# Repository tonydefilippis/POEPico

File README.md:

# POE Pico
"POE Pico" is a PCBA design for a RP2040 "Pi Pico" configured to support 40W active POE with Ethernet <-> USB conversion. 
# Diagram
Pre-print, the following 3D Views are available, but are not fully representative of the final product:
<br />Top<br />

<br />Bottom<br />

A PDF export of the schematic sheets for reference can be found [here](documentation/POEPico.pdf).
# Feature List
## Components
The USB to Ethernet conversion IC is a [LAN9500A](https://www.microchip.com/en-us/product/lan9500a). The board features a 40W active POE power/data supply input with a fully-isolated 12 VDC @ 2A Flyback courtesy of an [LT4295](https://www.analog.com/media/en/technical-documentation/data-sheets/LT4295.pdf). Downstream of the flyback is a 12V to 5V buck converter and 3.3V power rails. Ethernet magnetics and LEDs are fully integrated by the RJ45 connector. 

Alternatively, the board supports bringup of the RP2040 and power through the Micro-B connector. Powering the PCBA through the 5V Micro-B connector will also power the 3.3V rail. 
## Pins
Header pins expose standard RP2040 GPIO, including an isolated 12V, 5V, and 3.3V power rail.
| Purpose | Pin | Pin | Purpose | 
| -------- | ------- | ------- | ------- |
| GND | J21.1 | J21.2 | +3V3 |
| GND | J21.3 | J21.4 | GPIO0 |
| GND | J21.5 | J21.6 | GPIO1 |
| GND | J21.7 | J21.8 | GPIO2 |
| GND | J21.9 | J21.10 | GPIO3 |
| GND | J21.11 | J21.12 | GPIO4 |
| GND | J21.13 | J21.14 | GPIO5 |
| GND | J21.15 | J21.16 | GPIO6 |
| GND | J21.17 | J21.18 | GPIO7 |
| GND | J21.19 | J21.20 | GPIO8 |
| GND | J21.21 | J21.22 | GPIO9 |
| GND | J21.23 | J21.24 | GPIO10 |
| GND | J21.25 | J21.26 | GPIO11 |
| GND | J21.27 | J21.28 | GPIO12 |
| GND | J21.29 | J21.30 | GPIO13 |
| GND | J21.31 | J21.32 | GPIO14 |
| GND | J21.33 | J21.34 | GPIO15 |
| GND | J21.35 | J21.36 | +5V0 |

| Purpose | Pin | Pin | Purpose |
| -------- | ------- | ------- | ------- |
| SWCLK | J22.1 | J22.2 | GND |
| SWD | J22.3 | J22.4 | GND |
| RUN | J22.5 | J22.6 | GND |
| GPIO16 | J22.7 | J22.8 | GND |
| GPIO17 | J22.9 | J22.10 | GND |
| GPIO18 | J22.11 | J22.12 | GND |
| GPIO19 | J22.13 | J22.14 | GND |
| GPIO20 | J22.15 | J22.16 | GND |
| GPIO21 | J22.17 | J22.18 | GND |
| GPIO22 | J22.19 | J22.20 | GND |
| GPIO23 | J22.21 | J22.22 | GND |
| GPIO24 | J22.23 | J22.24 | GND |
| GPIO25 | J22.25 | J22.26 | GND |
| GPIO26 | J22.27 | J22.28 | GND |
| GPIO27 | J22.29 | J22.30 | GND |
| GPIO28 | J22.31 | J22.32 | GND |
| GPIO29 | J22.33 | J22.34 | GND |
| +12V0 | J22.35 | J22.26 | GND |

# Assembly
To be assembled as a 4-layer PCB, with associated BOM. Components to be placed on top and bottom of board. BOM has been edited to support JLCPCB quoting. Approximate cost estimate as of 21/10/2024 is $60/pc, including fabrication, components, assembly, and shipping.

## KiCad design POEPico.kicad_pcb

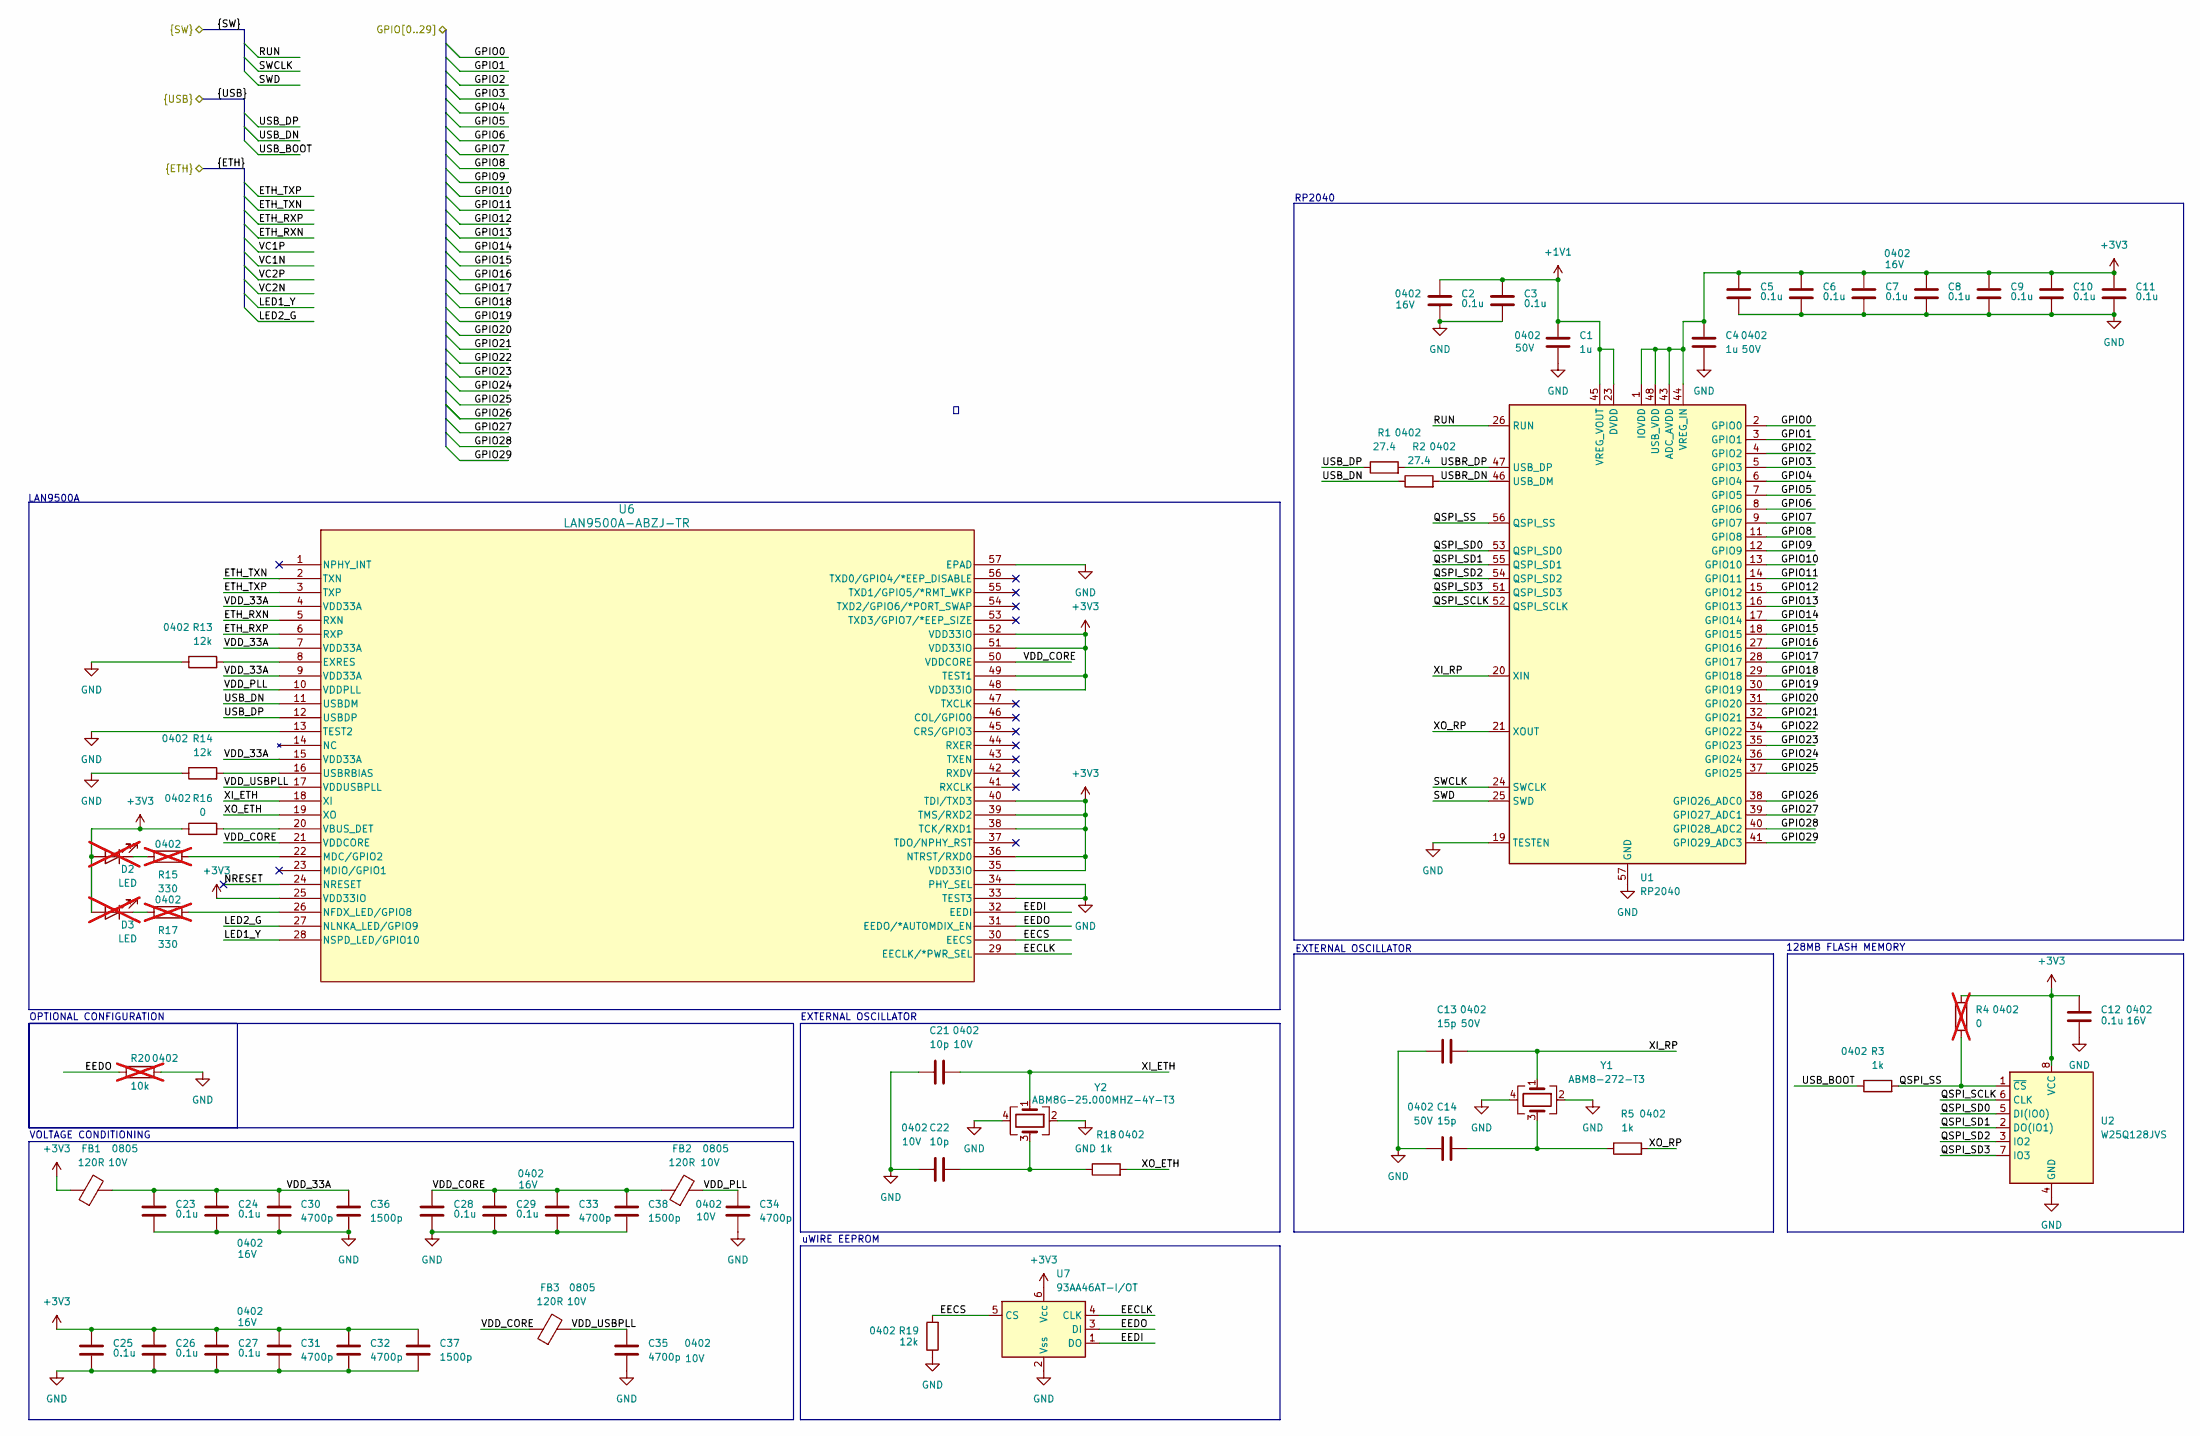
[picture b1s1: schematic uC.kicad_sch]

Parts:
C1, C4: 1u; C_0402_1005Metric; Rating 50V; PART-NUMBER C1518208
C2, C3, C5, C6, C7, C8, C9, C10, C11, C12, C23, C24, C25, C26, C27, C28, C29: 0.1u; C_0402_1005Metric; Rating 16V; PART-NUMBER C1525
C13, C14: 15p; C_0402_1005Metric; Rating 50V; PART-NUMBER C1548
C21, C22: 10p; C_0402_1005Metric; Rating 10V; PART-NUMBER C1545
C30, C31, C32, C33, C34, C35: 4700p; C_0402_1005Metric; Rating 10V; PART-NUMBER C7503510
C36, C37, C38: 1500p; C_0402_1005Metric; Rating 50V; PART-NUMBER C284989
D2, D3: LED; LED_0603; Rating 3.3V; not fitted
FB1, FB2, FB3: 120R; L_Eaton_MCL2012V1; Rating 10V; PART-NUMBER C88990
R1, R2: 27.4; R_0402_1005Metric; PART-NUMBER C284479
R3, R5, R18: 1k; R_0402_1005Metric; PART-NUMBER C106235
R4: 0; R_0402_1005Metric; PART-NUMBER C17168; not fitted
R13, R14, R19: 12k; R_0402_1005Metric; PART-NUMBER C102781
R15, R17: 330; R_0402_1005Metric; PART-NUMBER C25104; not fitted
R16: 0; R_0402_1005Metric; PART-NUMBER C17168
R20: 10k; R_0402_1005Metric; PART-NUMBER C60490; not fitted
U1: RP2040; QFN-56-1EP_7x7mm_P0.4mm_EP3.2x3.2mm; PART-NUMBER C2040
U2: W25Q128JVS; SOIC-8_5.23x5.23mm_P1.27mm; PART-NUMBER C97521
U6: LAN9500A-ABZJ-TR; QFN-56-1EP_8x8mm_P0.5mm_EP4.3x4.3mm; PART-NUMBER C2651877
U7: 93AA46AT-I/OT; SOT-23-6; PART-NUMBER C145736
Y1: ABM8-272-T3; 4-SMD_2.35x2.95mm; PART-NUMBER C20625731
Y2: ABM8G-25.000MHZ-4Y-T3; 4-SMD_2.35x2.95mm; PART-NUMBER C596914

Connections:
+1V1: C1.2, C2.1, C3.1, U1.23 (DVDD), U1.45 (VREG_VOUT), U1.50 (DVDD)
+3V3: C4.2, C5.1, C6.1, C7.1, C8.1, C9.1, C10.1, C11.1, C12.1, C25.1, C26.1, C27.1, C31.1, C32.1, C37.1, D2.2 (A), D3.2 (A), FB1.1, R4.1, R16.1, U1.1 (IOVDD), U1.10 (IOVDD), U1.22 (IOVDD), U1.33 (IOVDD), U1.42 (IOVDD), U1.43 (ADC_AVDD), U1.44 (VREG_IN), U1.48 (USB_VDD), U1.49 (IOVDD), U2.8 (VCC), U6.25 (VDD33IO), U6.35 (VDD33IO), U6.36 (NTRST/RXD0), U6.38 (TCK/RXD1), U6.39 (TMS/RXD2), U6.40 (TDI/TXD3), U6.48 (VDD33IO), U6.49 (TEST1), U6.51 (VDD33IO), U6.52 (VDD33IO), U7.6 (Vcc); also elsewhere on the board
/Connectors/ETH_RXN: U6.5 (RXN); also elsewhere on the board
/Connectors/ETH_RXP: U6.6 (RXP); also elsewhere on the board
/Connectors/ETH_TXN: U6.2 (TXN); also elsewhere on the board
/Connectors/ETH_TXP: U6.3 (TXP); also elsewhere on the board
/Connectors/GPIO0: U1.2 (GPIO0); also elsewhere on the board
/Connectors/GPIO1: U1.3 (GPIO1); also elsewhere on the board
/Connectors/GPIO2: U1.4 (GPIO2); also elsewhere on the board
/Connectors/GPIO3: U1.5 (GPIO3); also elsewhere on the board
/Connectors/GPIO4: U1.6 (GPIO4); also elsewhere on the board
/Connectors/GPIO5: U1.7 (GPIO5); also elsewhere on the board
/Connectors/GPIO6: U1.8 (GPIO6); also elsewhere on the board
/Connectors/GPIO7: U1.9 (GPIO7); also elsewhere on the board
/Connectors/GPIO8: U1.11 (GPIO8); also elsewhere on the board
/Connectors/GPIO9: U1.12 (GPIO9); also elsewhere on the board
/Connectors/GPIO10: U1.13 (GPIO10); also elsewhere on the board
/Connectors/GPIO11: U1.14 (GPIO11); also elsewhere on the board
/Connectors/GPIO12: U1.15 (GPIO12); also elsewhere on the board
/Connectors/GPIO13: U1.16 (GPIO13); also elsewhere on the board
/Connectors/GPIO14: U1.17 (GPIO14); also elsewhere on the board
/Connectors/GPIO15: U1.18 (GPIO15); also elsewhere on the board
/Connectors/GPIO16: U1.27 (GPIO16); also elsewhere on the board
/Connectors/GPIO17: U1.28 (GPIO17); also elsewhere on the board
/Connectors/GPIO18: U1.29 (GPIO18); also elsewhere on the board
/Connectors/GPIO19: U1.30 (GPIO19); also elsewhere on the board
/Connectors/GPIO20: U1.31 (GPIO20); also elsewhere on the board
/Connectors/GPIO21: U1.32 (GPIO21); also elsewhere on the board
/Connectors/GPIO22: U1.34 (GPIO22); also elsewhere on the board
/Connectors/GPIO23: U1.35 (GPIO23); also elsewhere on the board
/Connectors/GPIO24: U1.36 (GPIO24); also elsewhere on the board
/Connectors/GPIO25: U1.37 (GPIO25); also elsewhere on the board
/Connectors/GPIO26: U1.38 (GPIO26_ADC0); also elsewhere on the board
/Connectors/GPIO27: U1.39 (GPIO27_ADC1); also elsewhere on the board
/Connectors/GPIO28: U1.40 (GPIO28_ADC2); also elsewhere on the board
/Connectors/GPIO29: U1.41 (GPIO29_ADC3); also elsewhere on the board
/Connectors/LED1_Y: U6.28 (NSPD_LED/GPIO10); also elsewhere on the board
/Connectors/LED2_G: U6.27 (NLNKA_LED/GPIO9); also elsewhere on the board
/Connectors/RUN: U1.26 (RUN); also elsewhere on the board
/Connectors/SWCLK: U1.24 (SWCLK); also elsewhere on the board
/Connectors/SWD: U1.25 (SWD); also elsewhere on the board
/Connectors/USB_BOOT: R3.1; also elsewhere on the board
/Connectors/USB_DN: R2.1, U6.11 (USBDM); also elsewhere on the board
/Connectors/USB_DP: R1.1, U6.12 (USBDP); also elsewhere on the board
/MicroController/EECLK: U6.29 (EECLK/*PWR_SEL), U7.4 (CLK)
/MicroController/EECS: R19.2, U6.30 (EECS), U7.5 (CS)
/MicroController/EEDI: U6.32 (EEDI), U7.1 (DO)
/MicroController/EEDO: R20.1, U6.31 (EEDO/*AUTOMDIX_EN), U7.3 (DI)
/MicroController/NRESET: U6.24 (NRESET)
/MicroController/QSPI_SCLK: U1.52 (QSPI_SCLK), U2.6 (CLK)
/MicroController/QSPI_SD0: U1.53 (QSPI_SD0), U2.5 (DI(IO0))
/MicroController/QSPI_SD1: U1.55 (QSPI_SD1), U2.2 (DO(IO1))
/MicroController/QSPI_SD2: U1.54 (QSPI_SD2), U2.3 (IO2)
/MicroController/QSPI_SD3: U1.51 (QSPI_SD3), U2.7 (IO3)
/MicroController/QSPI_SS: R3.2, R4.2, U1.56 (QSPI_SS), U2.1 (~CS)
/MicroController/USBR_DN: R2.2, U1.46 (USB_DM)
/MicroController/USBR_DP: R1.2, U1.47 (USB_DP)
/MicroController/VDD_33A: C23.1, C24.1, C30.1, C36.1, FB1.2, U6.4 (VDD33A), U6.7 (VDD33A), U6.9 (VDD33A), U6.15 (VDD33A)
/MicroController/VDD_CORE: C28.1, C29.1, C33.1, C38.1, FB2.1, FB3.1, U6.21 (VDDCORE), U6.50 (VDDCORE)
/MicroController/VDD_PLL: C34.1, FB2.2, U6.10 (VDDPLL)
/MicroController/VDD_USBPLL: C35.1, FB3.2, U6.17 (VDDUSBPLL)
/MicroController/XI_ETH: C21.2, U6.18 (XI), Y2.1
/MicroController/XI_RP: C13.2, U1.20 (XIN), Y1.1
/MicroController/XO_ETH: R18.2, U6.19 (XO)
/MicroController/XO_RP: R5.2, U1.21 (XOUT)
GND: C1.1, C2.2, C3.2, C4.1, C5.2, C6.2, C7.2, C8.2, C9.2, C10.2, C11.2, C12.2, C13.1, C14.1, C21.1, C22.1, C23.2, C24.2, C25.2, C26.2, C27.2, C28.2, C29.2, C30.2, C31.2, C32.2, C33.2, C34.2, C35.2, C36.2, C37.2, C38.2, R13.1, R14.1, R19.1, R20.2, U1.19 (TESTEN), U1.57 (GND), U2.4 (GND), U6.13 (TEST2), U6.33 (TEST3), U6.34 (PHY_SEL), U6.57 (EPAD), U7.2 (Vss), Y1.2, Y1.4, Y2.2, Y2.4; also elsewhere on the board
unnamed: C14.2, R5.1, Y1.3
unnamed: C22.2, R18.1, Y2.3
unnamed: D2.1 (K), R15.1
unnamed: D3.1 (K), R17.1
unnamed: R13.2, U6.8 (EXRES)
unnamed: R15.2, U6.22 (MDC/GPIO2)
unnamed: R17.2, U6.26 (NFDX_LED/GPIO8)
unnamed: R14.2, U6.16 (USBRBIAS)
unnamed: R16.2, U6.20 (VBUS_DET)

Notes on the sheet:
EXTERNAL OSCILLATOR
LAN9500A
uWIRE EEPROM
OPTIONAL CONFIGURATION
RP2040
128MB FLASH MEMORY
VOLTAGE CONDITIONING

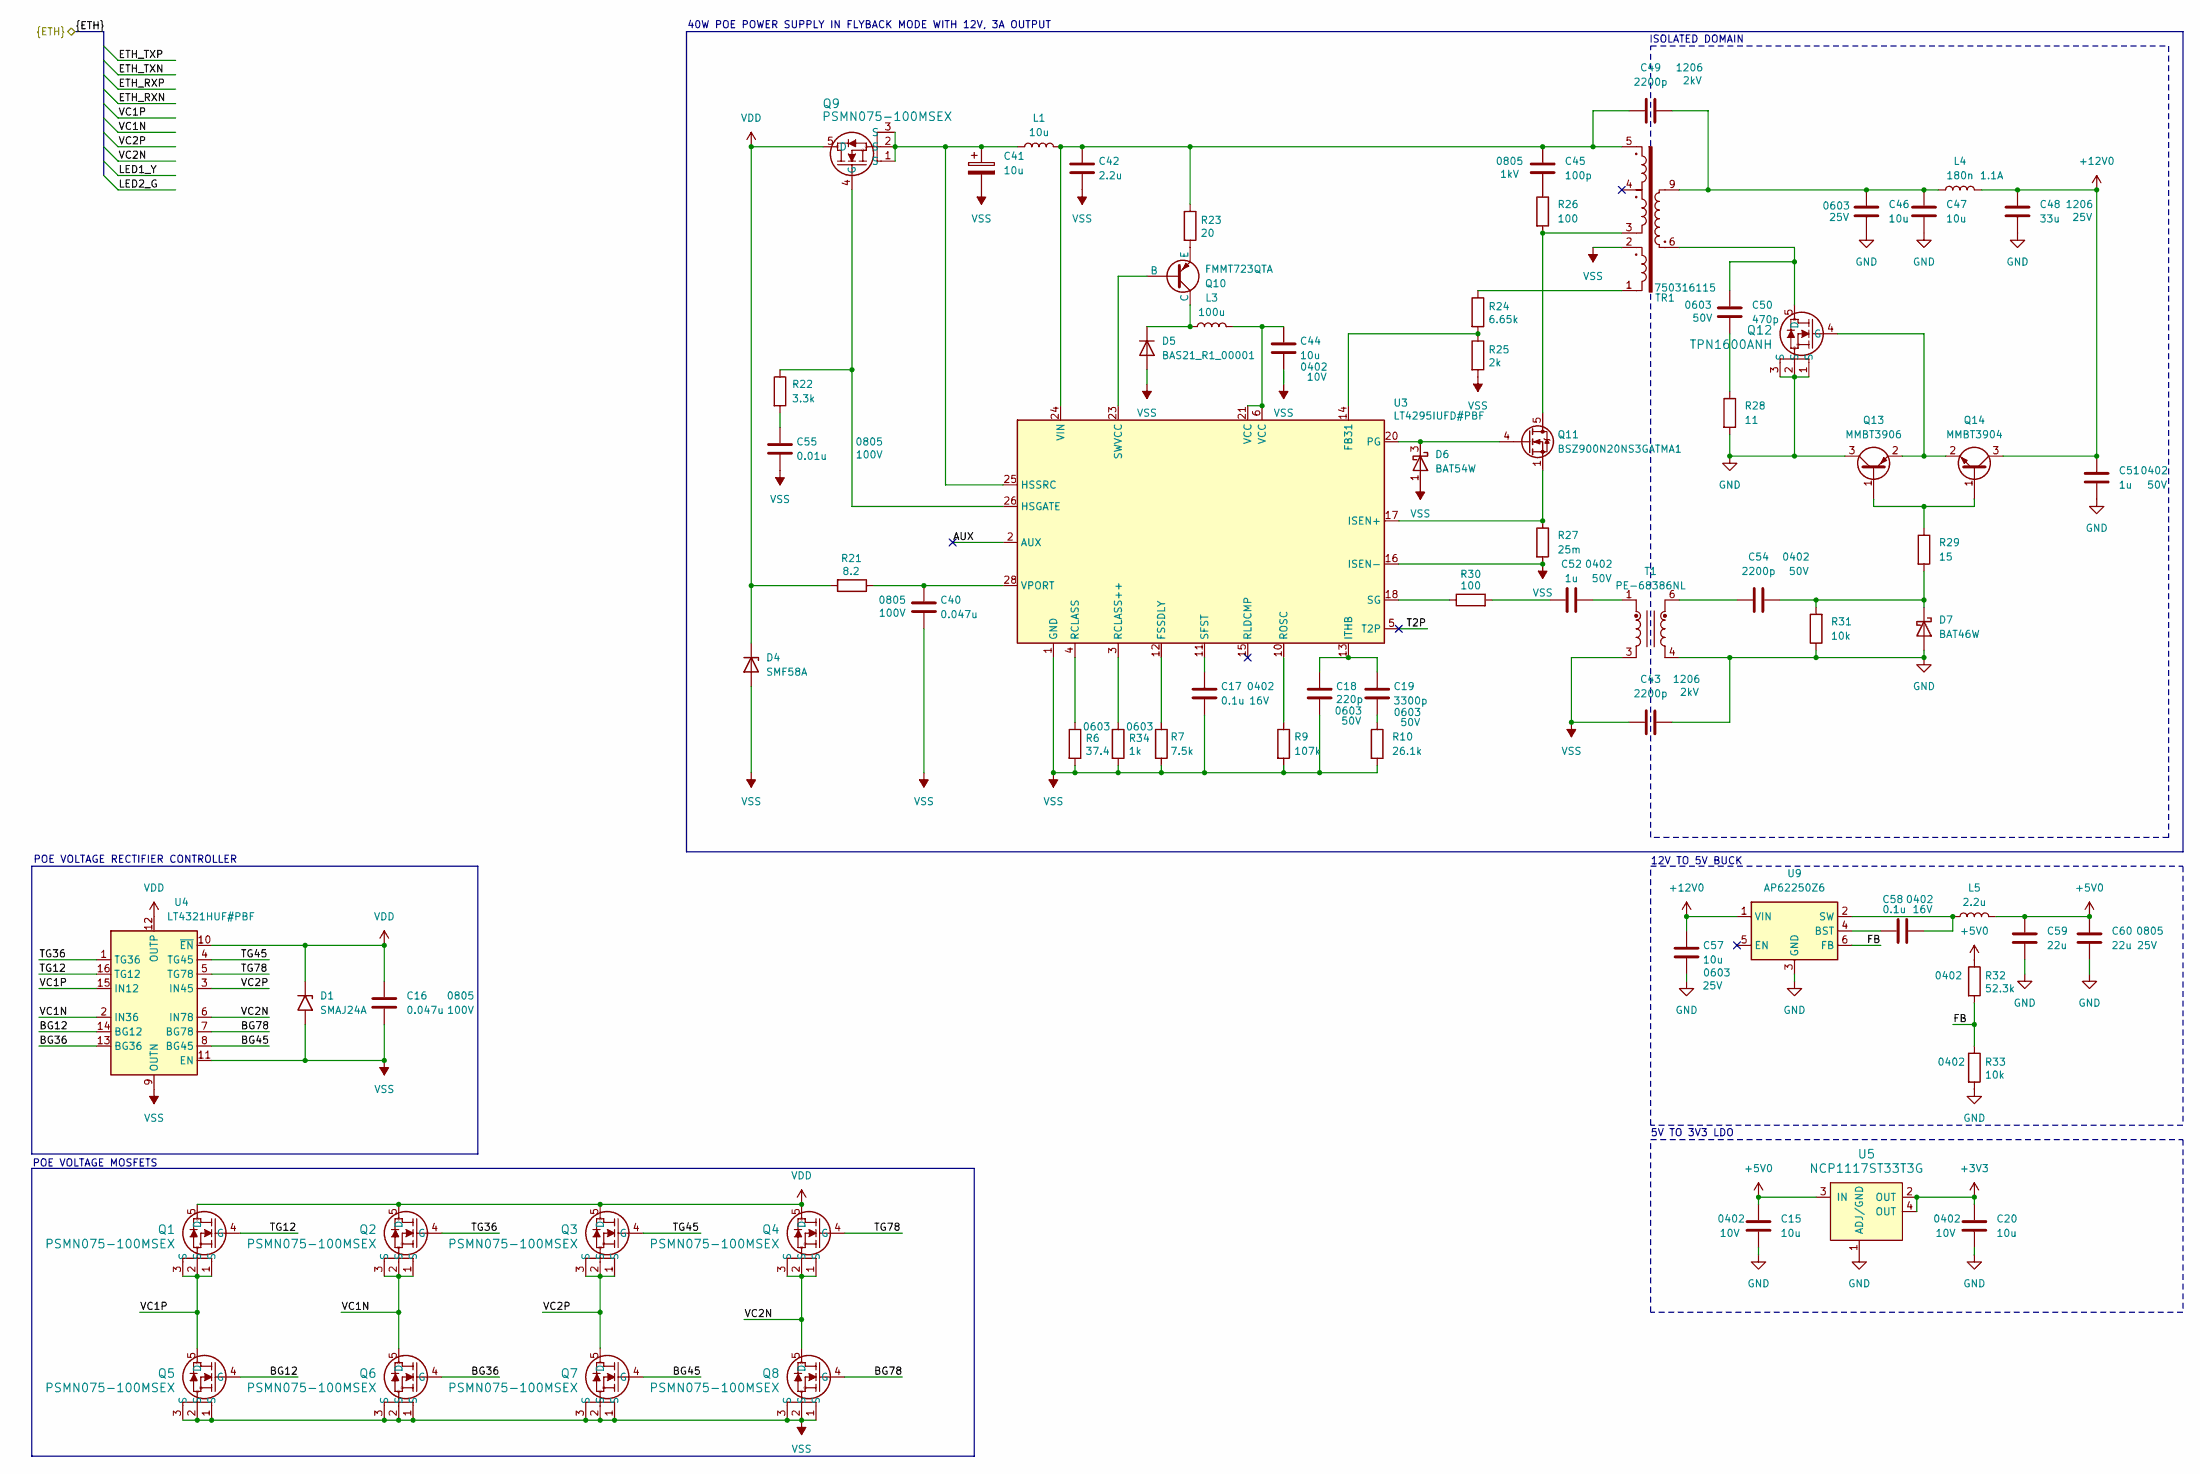
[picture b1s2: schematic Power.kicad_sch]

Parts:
C15, C20, C44: 10u; C_0402_1005Metric; Rating 10V; PART-NUMBER C77000
C16, C40: 0.047u; C_0805_2012Metric; Rating 100V; PART-NUMBER C5186810
C17, C58: 0.1u; C_0402_1005Metric; Rating 16V; PART-NUMBER C1525
C18: 220p; C_0603_1608Metric; Rating 50V; PART-NUMBER C2897613
C19: 3300p; C_0603_1608Metric; Rating 50V; PART-NUMBER C5182463
C41: 10u; C_1210_3225Metric; Rating 100V; PART-NUMBER C72482
C42: 2.2u; C_0805_2012Metric; Rating 100V; PART-NUMBER C6119935
C43, C49: 2200p; C_1206_3216Metric; Rating 2kV; PART-NUMBER C41018
C45: 100p; C_0805_2012Metric; Rating 1kV; PART-NUMBER C967584
C46, C47, C57: 10u; C_0603_1608Metric; Rating 25V; PART-NUMBER C96446
C48: 33u; C_1206_3216Metric; Rating 25V; PART-NUMBER C342307
C50: 470p; C_0603_1608Metric; Rating 50V; PART-NUMBER C1620
C51, C52: 1u; C_0402_1005Metric; Rating 50V; PART-NUMBER C1518208
C54: 2200p; C_0402_1005Metric; Rating 50V; PART-NUMBER C915853
C55: 0.01u; C_0805_2012Metric; Rating 100V; PART-NUMBER C7503490
C59, C60: 22u; C_0402_1005Metric; Rating 25V; PART-NUMBER C45783
D1: SMAJ24A; D_SMA; PART-NUMBER C10769
D4: SMF58A; D_SOD-123; PART-NUMBER C435457
D5: BAS21_R1_00001; TSOT-23; PART-NUMBER C391392
D6: BAT54W; SOT-323_SC-70; PART-NUMBER C5186013
D7: BAT46W; D_SOD-123; PART-NUMBER C5805641
L1: 10u; FCH5030-100M; PART-NUMBER C20415529
L3: 100u; AABG05A20M101; PART-NUMBER C5119206
L4: 180n; L_0603_1608Metric; Rating 1.1A; PART-NUMBER C251952
L5: 2.2u; L_Murata_DFE201610P; PART-NUMBER C337891
Q1, Q2, Q3, Q4, Q5, Q6, Q7, Q8, Q9: PSMN075-100MSEX; LFPAK33_SOT1210_NEX; PART-NUMBER C478016
Q10: FMMT723QTA; TSOT-23; PART-NUMBER C5249004
Q11: BSZ900N20NS3GATMA1; TDSON-8-1; PART-NUMBER C3279283
Q12: TPN1600ANH; TDSON-8-1; PART-NUMBER C24363903
Q13: MMBT3906; SOT-23; PART-NUMBER C7420354
Q14: MMBT3904; SOT-23; PART-NUMBER C7420353
R6: 37.4; R_0603_1608Metric; PART-NUMBER C25195
R7: 7.5k; R_0603_1608Metric; PART-NUMBER C23234
R9: 107k; R_0603_1608Metric; PART-NUMBER C14889
R10: 26.1k; R_0603_1608Metric; PART-NUMBER C23356
R21: 8.2; R_0603_1608Metric; PART-NUMBER C23247
R22: 3.3k; R_0603_1608Metric; PART-NUMBER C22978
R23: 20; R_0603_1608Metric; PART-NUMBER C22950
R24: 6.65k; R_0603_1608Metric; PART-NUMBER C3016441
R25: 2k; R_0603_1608Metric; PART-NUMBER C22975
R26: 100; R_0805_2012Metric; Rating 1/2W; PART-NUMBER C441975
R27: 25m; R_0805_2012Metric; Rating 1/4W; PART-NUMBER C2767472
R28: 11; R_1210_3225Metric; Rating 1/2W; PART-NUMBER C422425
R29: 15; R_0603_1608Metric; PART-NUMBER C22810
R30: 100; R_0603_1608Metric; PART-NUMBER C22775
R31, R33: 10k; R_0402_1005Metric; PART-NUMBER C60490
R32: 52.3k; R_0402_1005Metric; PART-NUMBER C26982
R34: 1k; R_0603_1608Metric; PART-NUMBER C21190
T1: PE-68386NL; Pulse_PA2001NL; PART-NUMBER C581397
TR1: 750316115; PART-NUMBER C24363903
U3: LT4295IUFD#PBF; QFN-28-1EP_4x5mm_P0.5mm_EP2.65x3.65mm; PART-NUMBER C672449
U4: LT4321HUF#PBF; QFN-16-1EP_4x4mm_P0.65mm_EP2.15x2.15mm; PART-NUMBER C672474
U5: NCP1117ST33T3G; SOT-223; PART-NUMBER C26537
U9: AP62250Z6; SOT-563; PART-NUMBER C5290220

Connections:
+3V3: C20.1, U5.2 (OUT), U5.4 (OUT); also elsewhere on the board
+5V0: C15.1, C59.1, C60.1, L5.2, R32.1, U5.3 (IN); also elsewhere on the board
+12V0: C48.1, C51.1, C57.1, L4.2, Q14.3 (C), U9.1 (VIN); also elsewhere on the board
/Connectors/VC1N: Q2.1 (S), Q2.2 (S), Q2.3 (S), Q6.5 (D), U4.2 (IN36); also elsewhere on the board
/Connectors/VC1P: Q1.1 (S), Q1.2 (S), Q1.3 (S), Q5.5 (D), U4.15 (IN12); also elsewhere on the board
/Connectors/VC2N: Q4.1 (S), Q4.2 (S), Q4.3 (S), Q8.5 (D), U4.6 (IN78); also elsewhere on the board
/Connectors/VC2P: Q3.1 (S), Q3.2 (S), Q3.3 (S), Q7.5 (D), U4.3 (IN45); also elsewhere on the board
/Power/AUX: U3.2 (AUX)
/Power/BG12: Q5.4 (G), U4.14 (BG12)
/Power/BG36: Q6.4 (G), U4.13 (BG36)
/Power/BG45: Q7.4 (G), U4.8 (BG45)
/Power/BG78: Q8.4 (G), U4.7 (BG78)
/Power/FB: R32.2, R33.1, U9.6 (FB)
/Power/T2P: U3.5 (T2P)
/Power/TG12: Q1.4 (G), U4.16 (TG12)
/Power/TG36: Q2.4 (G), U4.1 (TG36)
/Power/TG45: Q3.4 (G), U4.4 (TG45)
/Power/TG78: Q4.4 (G), U4.5 (TG78)
GND: C15.2, C20.2, C43.2, C46.2, C47.2, C48.2, C51.2, C57.2, C59.2, C60.2, D7.2 (A), Q12.1 (S), Q12.2 (S), Q12.3 (S), Q13.3 (C), R28.2, R31.1, R33.2, T1.4, U5.1 (ADJ/GND), U9.3 (GND); also elsewhere on the board
unnamed: C19.2, R10.1
unnamed: C44.1, L3.2, U3.6 (VCC), U3.7 (VCC), U3.8 (VCC), U3.9 (VCC), U3.21 (VCC)
unnamed: C45.2, R26.1
unnamed: C46.1, C47.1, C49.2, L4.1, TR1.9, TR1.10
unnamed: C50.2, R28.1
unnamed: C52.1, R30.2
unnamed: C52.2, T1.1
unnamed: C54.1, T1.6
unnamed: C55.1, R22.2
unnamed: D5.3 (K), L3.1, Q10.1 (C)
unnamed: D6.3 (K), Q11.4 (G), U3.20 (PG)
unnamed: C54.2, D7.1 (K), R29.2, R31.2
unnamed: Q9.4 (G), R22.1, U3.26 (HSGATE)
unnamed: Q10.2 (B), U3.23 (SWVCC)
unnamed: Q10.3 (E), R23.2
unnamed: Q11.5 (D), R26.2, TR1.3
unnamed: C50.1, Q12.5 (D), TR1.6, TR1.7
unnamed: Q12.4 (G), Q13.2 (E), Q14.2 (E)
unnamed: Q13.1 (B), Q14.1 (B), R29.1
unnamed: R24.1, TR1.1
unnamed: R24.2, R25.1, U3.14 (FB31)
unnamed: R7.1, U3.12 (FSSDLY)
unnamed: C41.1, L1.1, Q9.1 (S), Q9.2 (S), Q9.3 (S), U3.25 (HSSRC)
unnamed: Q11.1 (S), Q11.2 (S), Q11.3 (S), R27.1, U3.17 (ISEN+)
unnamed: C18.1, C19.1, U3.13 (ITHB)
unnamed: R6.1, U3.4 (RCLASS)
unnamed: R34.1, U3.3 (RCLASS++)
unnamed: R9.1, U3.10 (ROSC)
unnamed: C17.1, U3.11 (SFST)
unnamed: R30.1, U3.18 (SG)
unnamed: C42.1, C45.1, C49.1, L1.2, R23.1, TR1.5, U3.24 (VIN)
unnamed: C40.1, R21.1, U3.28 (VPORT)
unnamed: C58.1, U9.4 (BST)
unnamed: C58.2, L5.1, U9.2 (SW)
VDD: C16.1, D1.1 (A1), D4.1 (K), Q1.5 (D), Q2.5 (D), Q3.5 (D), Q4.5 (D), Q9.5 (D), R21.2, U4.10 (~EN), U4.12 (OUTP)
VSS: C16.2, C17.2, C18.2, C40.2, C41.2, C42.2, C43.1, C44.2, C55.2, D1.2 (A2), D4.2 (A), D5.1 (A), D6.1 (A), Q5.1 (S), Q5.2 (S), Q5.3 (S), Q6.1 (S), Q6.2 (S), Q6.3 (S), Q7.1 (S), Q7.2 (S), Q7.3 (S), Q8.1 (S), Q8.2 (S), Q8.3 (S), R6.2, R7.2, R9.2, R10.2, R25.2, R27.2, R34.2, T1.3, TR1.2, U3.1 (GND), U3.16 (ISEN-), U3.19 (GND), U3.29 (GND), U4.9 (OUTN), U4.11 (EN), U4.17 (OUTN)

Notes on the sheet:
5V TO 3V3 LDO
POE VOLTAGE RECTIFIER CONTROLLER
12V TO 5V BUCK
POE VOLTAGE MOSFETS
ISOLATED DOMAIN
40W POE POWER SUPPLY IN FLYBACK MODE WITH 12V, 3A OUTPUT

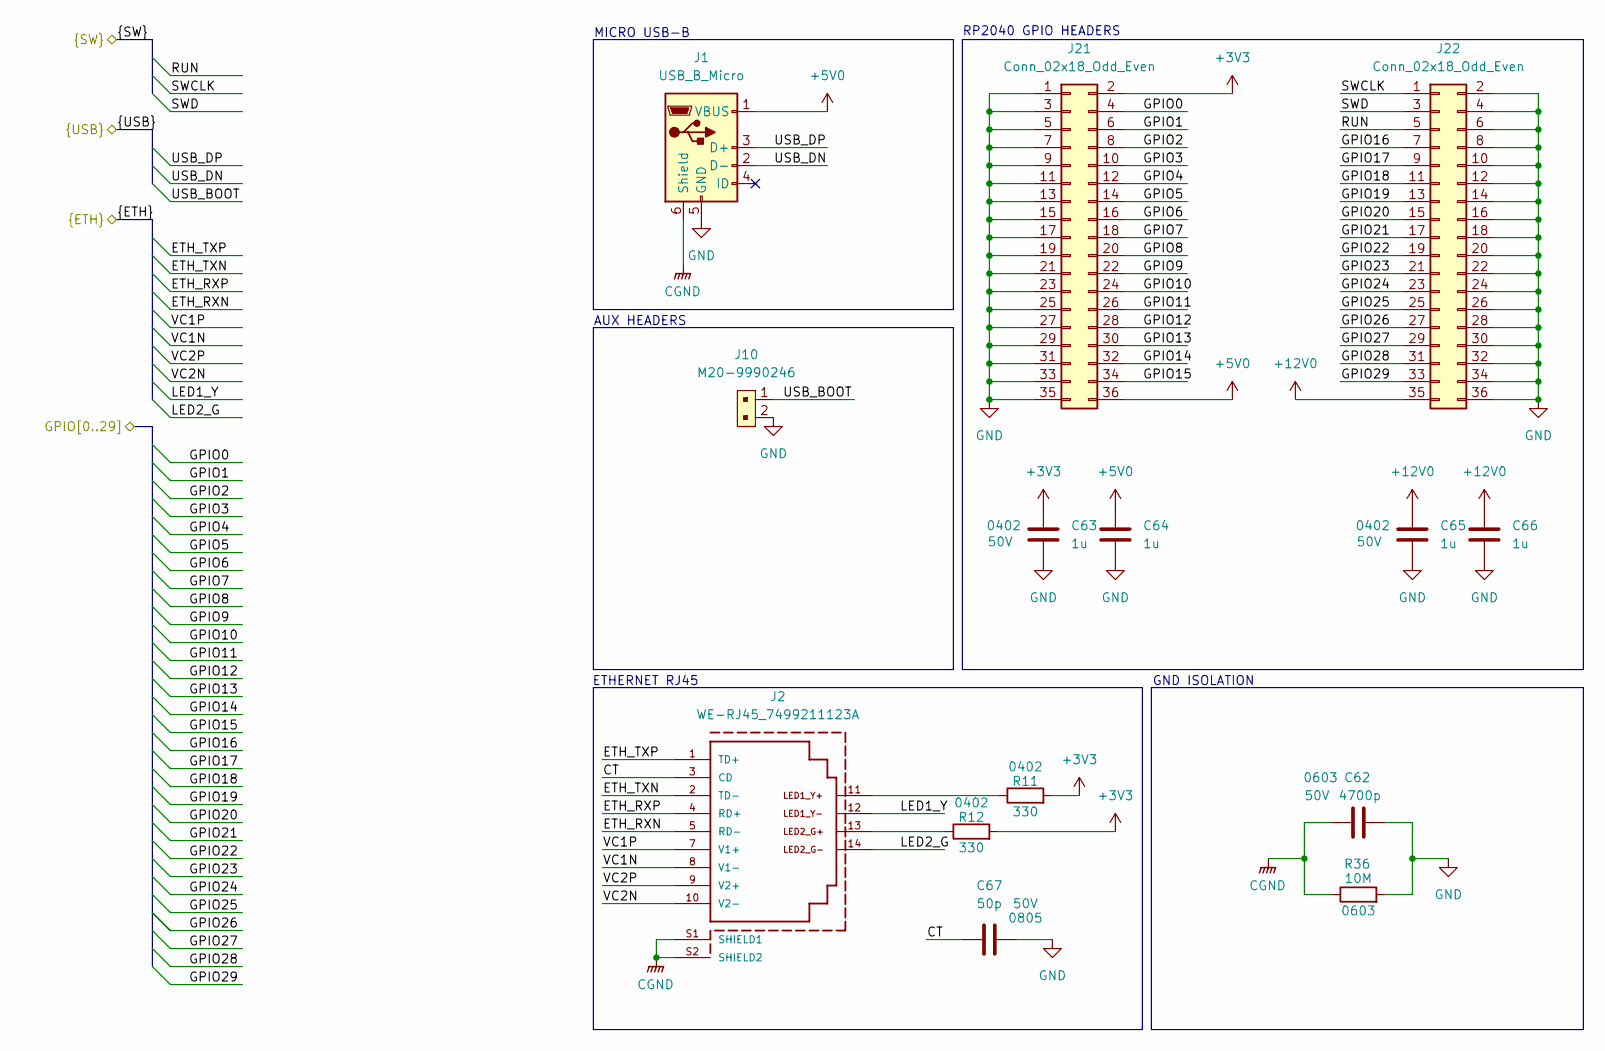
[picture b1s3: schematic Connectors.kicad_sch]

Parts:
C62: 4700p; C_0603_1608Metric; Rating 50V; PART-NUMBER C7503499
C63, C64, C65, C66: 1u; C_0402_1005Metric; Rating 50V; PART-NUMBER C1518208
C67: 50p; C_0805_2012Metric; Rating 50V; PART-NUMBER C1823
J1: USB_B_Micro; USB_Micro-B_Amphenol_10103594-0001LF_Horizontal; PART-NUMBER C428495
J2: WE-RJ45_7499211123A; 7499211123A; PART-NUMBER C24363903
J10: M20-9990246; PinHeader_1x2_P2.54mm; PART-NUMBER C706874
J21, J22: Conn_02x18_Odd_Even; PinHeader_2x18_P2.54mm_Vertical; PART-NUMBER C19184369
R11, R12: 330; R_0402_1005Metric; PART-NUMBER C25104
R36: 10M; R_0603_1608Metric; PART-NUMBER C7250

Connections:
+3V3: C63.2, J21.2, R11.2, R12.2; also elsewhere on the board
+5V0: C64.2, J1.1 (VBUS), J21.36; also elsewhere on the board
+12V0: C65.2, C66.2, J22.35; also elsewhere on the board
/Connectors/CT: C67.2, J2.3 (CD)
/Connectors/ETH_RXN: J2.5 (RD-); also elsewhere on the board
/Connectors/ETH_RXP: J2.4 (RD+); also elsewhere on the board
/Connectors/ETH_TXN: J2.2 (TD-); also elsewhere on the board
/Connectors/ETH_TXP: J2.1 (TD+); also elsewhere on the board
/Connectors/GPIO0: J21.4; also elsewhere on the board
/Connectors/GPIO1: J21.6; also elsewhere on the board
/Connectors/GPIO2: J21.8; also elsewhere on the board
/Connectors/GPIO3: J21.10; also elsewhere on the board
/Connectors/GPIO4: J21.12; also elsewhere on the board
/Connectors/GPIO5: J21.14; also elsewhere on the board
/Connectors/GPIO6: J21.16; also elsewhere on the board
/Connectors/GPIO7: J21.18; also elsewhere on the board
/Connectors/GPIO8: J21.20; also elsewhere on the board
/Connectors/GPIO9: J21.22; also elsewhere on the board
/Connectors/GPIO10: J21.24; also elsewhere on the board
/Connectors/GPIO11: J21.26; also elsewhere on the board
/Connectors/GPIO12: J21.28; also elsewhere on the board
/Connectors/GPIO13: J21.30; also elsewhere on the board
/Connectors/GPIO14: J21.32; also elsewhere on the board
/Connectors/GPIO15: J21.34; also elsewhere on the board
/Connectors/GPIO16: J22.7; also elsewhere on the board
/Connectors/GPIO17: J22.9; also elsewhere on the board
/Connectors/GPIO18: J22.11; also elsewhere on the board
/Connectors/GPIO19: J22.13; also elsewhere on the board
/Connectors/GPIO20: J22.15; also elsewhere on the board
/Connectors/GPIO21: J22.17; also elsewhere on the board
/Connectors/GPIO22: J22.19; also elsewhere on the board
/Connectors/GPIO23: J22.21; also elsewhere on the board
/Connectors/GPIO24: J22.23; also elsewhere on the board
/Connectors/GPIO25: J22.25; also elsewhere on the board
/Connectors/GPIO26: J22.27; also elsewhere on the board
/Connectors/GPIO27: J22.29; also elsewhere on the board
/Connectors/GPIO28: J22.31; also elsewhere on the board
/Connectors/GPIO29: J22.33; also elsewhere on the board
/Connectors/LED1_Y: J2.12; also elsewhere on the board
/Connectors/LED2_G: J2.14; also elsewhere on the board
/Connectors/RUN: J22.5; also elsewhere on the board
/Connectors/SWCLK: J22.1; also elsewhere on the board
/Connectors/SWD: J22.3; also elsewhere on the board
/Connectors/USB_BOOT: J10.1; also elsewhere on the board
/Connectors/USB_DN: J1.2 (D-); also elsewhere on the board
/Connectors/USB_DP: J1.3 (D+); also elsewhere on the board
/Connectors/VC1N: J2.8 (V1-); also elsewhere on the board
/Connectors/VC1P: J2.7 (V1+); also elsewhere on the board
/Connectors/VC2N: J2.10 (V2-); also elsewhere on the board
/Connectors/VC2P: J2.9 (V2+); also elsewhere on the board
CGND: C62.1, J1.6 (Shield), J2.S1 (SHIELD1), J2.S2 (SHIELD2), R36.1
GND: C62.2, C63.1, C64.1, C65.1, C66.1, C67.1, J1.5 (GND), J10.2, J21.1, J21.3, J21.5, J21.7, J21.9, J21.11, J21.13, J21.15, J21.17, J21.19, J21.21, J21.23, J21.25, J21.27, J21.29, J21.31, J21.33, J21.35, J22.2, J22.4, J22.6, J22.8, J22.10, J22.12, J22.14, J22.16, J22.18, J22.20, J22.22, J22.24, J22.26, J22.28, J22.30, J22.32, J22.34, J22.36, R36.2; also elsewhere on the board
unnamed: J2.11, R11.1
unnamed: J2.13, R12.1

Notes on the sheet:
GND ISOLATION
AUX HEADERS
MICRO USB-B
RP2040 GPIO HEADERS
ETHERNET RJ45

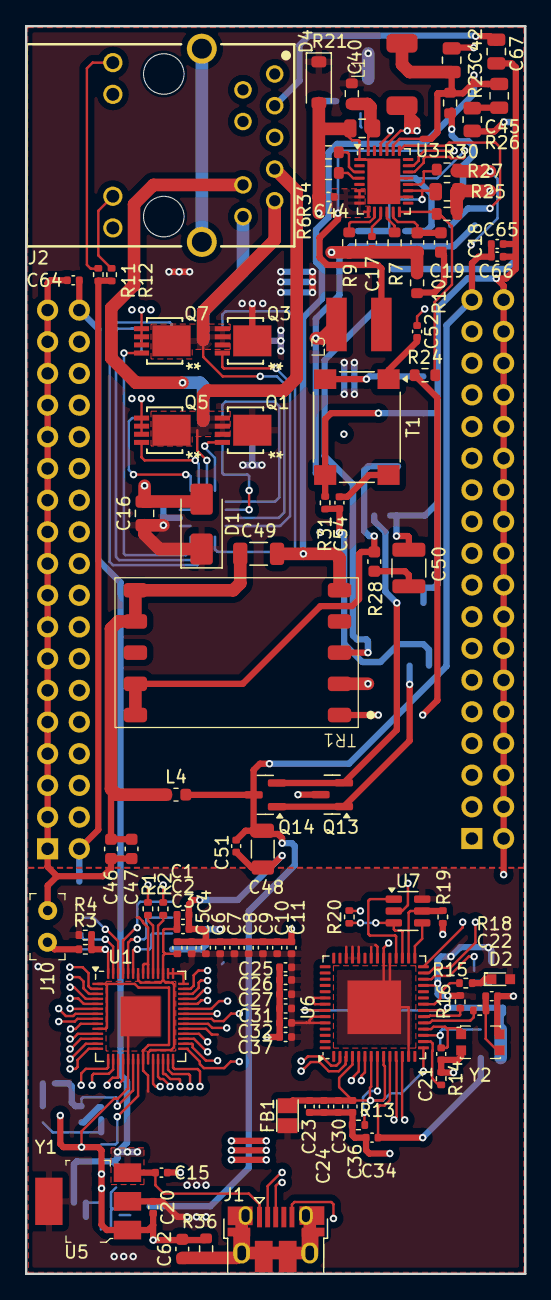
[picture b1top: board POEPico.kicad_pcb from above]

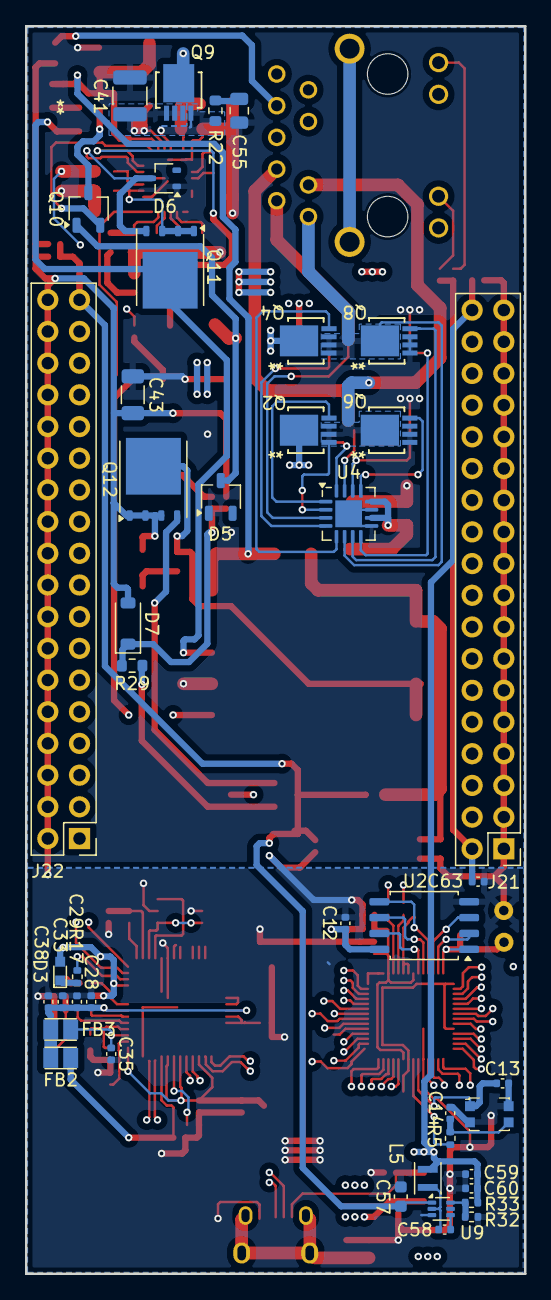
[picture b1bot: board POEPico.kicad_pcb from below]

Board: 4 copper layers, 40.0 x 100.0 mm, 142 parts (43 on the bottom side), 129 nets.

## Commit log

2024-10-11 Initial commit of project.
2024-10-11 Skeletonize readme
2024-10-11 Add GPL-3.0 license.
2024-10-21 BOM Cleanup and matching for JLCPCB, downstream edits to Schematic and Board. Added backup files to .gitignore.
2024-10-21 BOM Finalization, board cleanup.
2024-10-22 Adding exported PDF of schematics.
2024-10-22 Removed backups files after adding to .gitignore.
